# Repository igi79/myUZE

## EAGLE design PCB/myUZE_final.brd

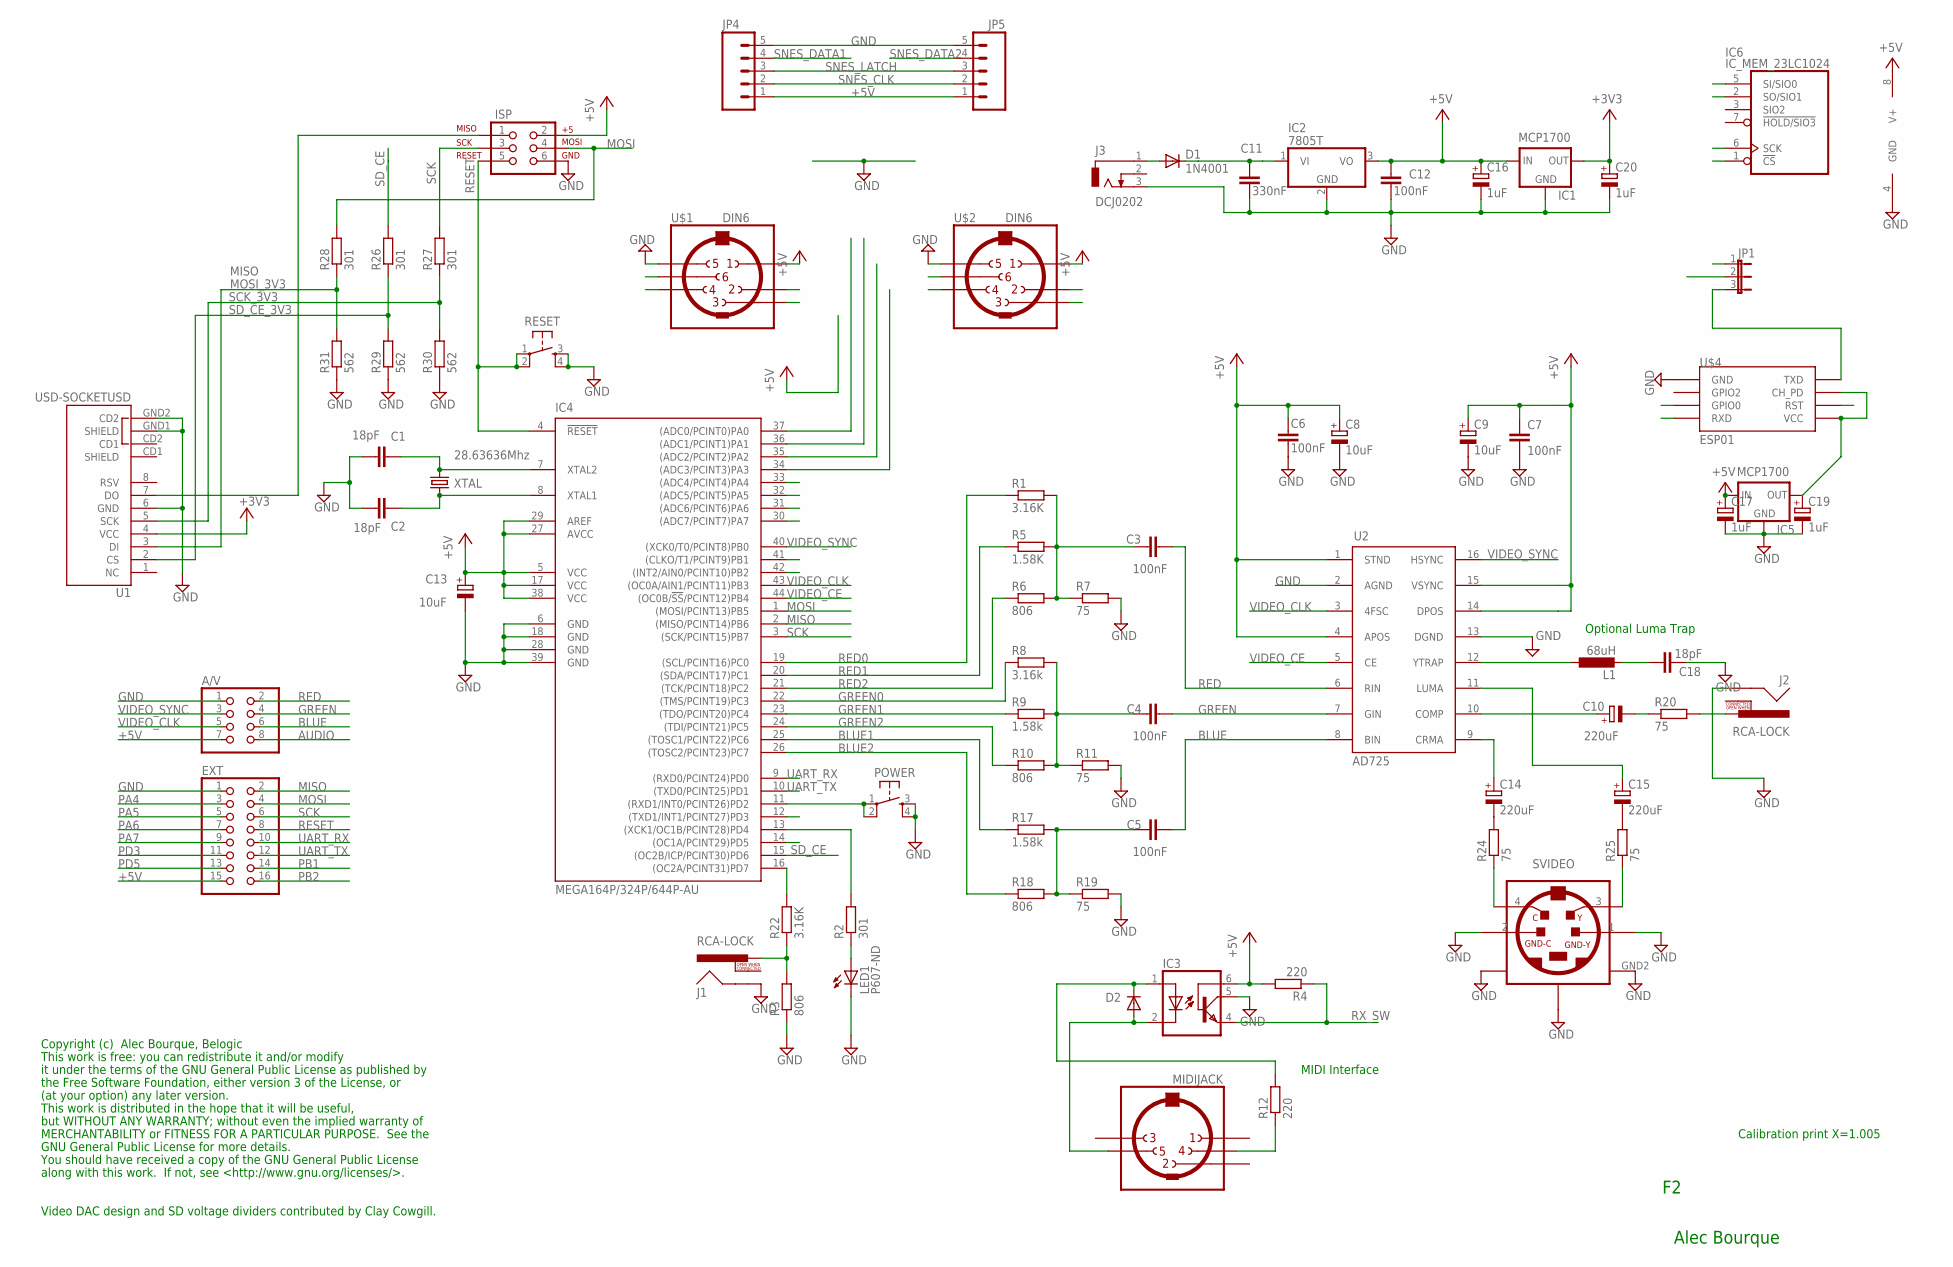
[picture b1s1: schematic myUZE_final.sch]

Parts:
A/V: PINHD-2X4; 2X04
AD725: AD725; SO16W
C1, C2, C18: 18pF; C0805
C3, C4, C5, C6, C7, C12: 100nF; C0805
C8, C9, C13: 10uF; 153CLV-0505
C10, C14, C15: 220uF; E2-5
C11: 330nF; C0805
C16, C17, C19, C20: 1uF; 153CLV-0505
D1: 1N4001; MELF-MLL41
D2: DIODE-MINIMELF; MINIMELF
EXT: PINHD-2X8; 2X08
IC1, IC5: MCP1700; TO92-INLINE
IC2: 7805T; TO220H
IC3: PC110; DIL06
IC4: MEGA164P/324P/644P-AU; TQFP44
IC6: IC_MEM_23LC1024; SOIC-8
ISP: AVR_SPI_PRG_6PTH; 2X3
J1, J2: RCA-LOCK; RCA_LOCK
J3: DCJ0202
JP1: JP2E; JP2
JP4, JP5: M05PTH; 1X05
L1: 68uH; IR-4
LED1: P607-ND; Q62902-B155
POWER: USER; TACTILE-PTH
R1, R22: 3.16K; R0805
R2, R26, R27, R28: 301; R0805
R3, R6, R10, R18: 806; R0805
R4, R12: 220; R0805
R5: 1.58K; R0805
R7, R11, R19, R20, R24, R25: 75; R0805
R8: 3.16k; R0805
R9, R17: 1.58k; R0805
R29, R30, R31: 562; R0805
RESET: RESET; TACTILE-PTH
SVIDEO: S-VIDEO OUT; MINIDIN4
U1: USD-SOCKETUSD; USD-SOCKET-PP
U$1, U$2: DIN6
U$4: ESP01
U$5: MIDIJACK; CP-2350
XTAL: 28.63636Mhz; HC49/S

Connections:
+3V3: C20.+, IC1.3 (OUT), U1.4 (VCC)
+5V: A/V.7, AD725.1 (STND), AD725.4 (APOS), AD725.14 (DPOS), AD725.15 (VSYNC), C6.1, C7.1, C8.+, C9.+, C12.1, C13.+, C16.+, C17.+, EXT.15, IC1.2 (IN), IC2.3 (VO), IC3.6 (BAS), IC4.5 (VCC), IC4.17 (VCC), IC4.27 (AVCC), IC4.29 (AREF), IC4.38 (VCC), IC5.2 (IN), IC6.8 (V+), ISP.2, JP4.1, JP5.1, R4.2, U$1.P1, U$2.P1
AUDIO: A/V.8, J1.PIN, R3.2, R22.1
BLUE: A/V.6, AD725.8 (BIN), C5.2
BLUE1: IC4.25 ((TOSC1/PCINT22)PC6), R17.1
BLUE2: IC4.26 ((TOSC2/PCINT23)PC7), R18.1
GND: A/V.1, AD725.2 (AGND), AD725.13 (DGND), C1.2, C2.2, C6.2, C7.2, C8.-, C9.-, C11.2, C12.2, C13.-, C16.-, C17.-, C18.2, C19.-, C20.-, EXT.1, IC1.1 (GND), IC2.2 (GND), IC3.5 (COL), IC4.6 (GND), IC4.18 (GND), IC4.28 (GND), IC4.39 (GND), IC5.1 (GND), IC6.4 (GND), ISP.6, J1.SHELL, J2.SHELL, J3.3, JP4.5, JP5.5, LED1.K (C), POWER.3, POWER.4, R3.1, R7.2, R11.2, R19.2, R29.1, R30.1, R31.1, RESET.3, RESET.4, SVIDEO.1 (GND-Y), SVIDEO.2 (GND-C), SVIDEO.GND1, SVIDEO.GND2, SVIDEO.GND3, U1.6 (GND), U1.GND1 (SHIELD), U1.GND2 (CD2), U$1.P5, U$2.P5, U$4.GND
GREEN: A/V.4, AD725.7 (GIN), C4.2
GREEN0: IC4.22 ((TMS/PCINT19)PC3), R8.1
GREEN1: IC4.23 ((TDO/PCINT20)PC4), R9.1
GREEN2: IC4.24 ((TDI/PCINT21)PC5), R10.1
MISO: EXT.2, IC4.2 ((MISO/PCINT14)PB6), IC6.2 (SO/SIO1), ISP.1, U1.7 (DO)
MOSI: EXT.4, IC4.1 ((MOSI/PCINT13)PB5), IC6.5 (SI/SIO0), ISP.4, R28.2
MOSI_3V3: R28.1, R31.2, U1.3 (DI)
unnamed: AD725.12 (YTRAP), L1.1
unnamed: C18.1, L1.2
unnamed: C5.1, R17.2, R18.2, R19.1
unnamed: C4.1, R8.2, R9.2, R10.2, R11.1
unnamed: C3.1, R1.2, R5.2, R6.2, R7.1
unnamed: C10.-, R20.1
unnamed: AD725.10 (COMP), C10.+
unnamed: J2.PIN, R20.2
unnamed: C1.1, IC4.7 (XTAL2), XTAL.2
unnamed: D1.A, J3.1
unnamed: C14.-, R24.2
unnamed: C2.1, IC4.8 (XTAL1), XTAL.1
unnamed: IC4.16 ((OC2A/PCINT31)PD7), R22.2
unnamed: D2.A, IC3.2 (C), U$5.5
unnamed: D2.C, IC3.1 (A), R12.2
unnamed: R12.1, U$5.4
unnamed: JP1.3, U$4.TX (TXD)
unnamed: C11.1, D1.C, IC2.1 (VI)
unnamed: C19.+, IC5.3 (OUT), U$4.CH_PD, U$4.VCC
unnamed: IC4.13 ((XCK1/OC1B/PCINT28)PD4), R2.2
unnamed: LED1.A, R2.1
unnamed: C15.-, R25.2
unnamed: AD725.11 (LUMA), C15.+
unnamed: AD725.9 (CRMA), C14.+
unnamed: R24.1, SVIDEO.4 (C)
unnamed: R25.1, SVIDEO.3 (Y)
PA4: EXT.3, IC4.33 ((ADC4/PCINT4)PA4), IC6.1 (!CS)
PA5: EXT.5, IC4.32 ((ADC5/PCINT5)PA5)
PA6: EXT.7, IC4.31 ((ADC6/PCINT6)PA6)
PA7: EXT.9, IC4.30 ((ADC7/PCINT7)PA7), U$4.GPIO0
PB1: EXT.14, IC4.41 ((CLKO/T1/PCINT9)PB1)
PB2: EXT.16, IC4.42 ((INT2/AIN0/PCINT10)PB2)
PD3: EXT.11, IC4.12 ((TXD1/INT1/PCINT27)PD3), U$4.RST
PD5: EXT.13, IC4.14 ((OC1A/PCINT29)PD5)
POWER_SW: IC4.11 ((RXD1/INT0/PCINT26)PD2), POWER.1, POWER.2
RED: A/V.2, AD725.6 (RIN), C3.2
RED0: IC4.19 ((SCL/PCINT16)PC0), R1.1
RED1: IC4.20 ((SDA/PCINT17)PC1), R5.1
RED2: IC4.21 ((TCK/PCINT18)PC2), R6.1
RESET: EXT.8, IC4.4 (!RESET), ISP.5, RESET.1, RESET.2
RX_SW: IC3.4 (EMI), JP1.1, R4.1
SCK: EXT.6, IC4.3 ((SCK/PCINT15)PB7), IC6.6 (SCK), ISP.3, R27.2
SCK_3V3: R27.1, R30.2, U1.5 (SCK)
SD_CE: IC4.15 ((OC2B/ICP/PCINT30)PD6), R26.2
SD_CE_3V3: R26.1, R29.2, U1.2 (CS)
SNES_CLK: IC4.34 ((ADC3/PCINT3)PA3), JP4.2, JP5.2, U$1.P2, U$2.P2
SNES_DATA1: IC4.37 ((ADC0/PCINT0)PA0), JP4.4, U$2.P4
SNES_DATA2: IC4.36 ((ADC1/PCINT1)PA1), JP5.4, U$1.P4
SNES_LATCH: IC4.35 ((ADC2/PCINT2)PA2), JP4.3, JP5.3, U$1.P3, U$2.P3
UART_RX: EXT.10, IC4.9 ((RXD0/PCINT24)PD0), JP1.2
UART_TX: EXT.12, IC4.10 ((TXD0/PCINT25)PD1), U$4.RX (RXD)
VIDEO_CE: AD725.5 (CE), IC4.44 ((OC0B/!SS!/PCINT12)PB4)
VIDEO_CLK: A/V.5, AD725.3 (4FSC), IC4.43 ((OC0A/AIN1/PCINT11)PB3)
VIDEO_SYNC: A/V.3, AD725.16 (HSYNC), IC4.40 ((XCK0/T0/PCINT8)PB0)

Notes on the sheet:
Optional Luma Trap
Alec Bourque
Copyright (c) Alec Bourque, Belogic
This work is free: you can redistribute it and/or modify
it under the terms of the GNU General Public License as published by
the Free Software Foundation, either version 3 of the License, or
(at your option) any later version.
This work is distributed in the hope that it will be useful,
but WITHOUT ANY WARRANTY; without even the implied warranty of
MERCHANTABILITY or FITNESS FOR A PARTICULAR PURPOSE. See the
GNU General Public License for more details.
You should have received a copy of the GNU General Public License
along with this work. If not, see <http://www.gnu.org/licenses/>.
MIDI Interface
Calibration print X=1.005
Video DAC design and SD voltage dividers contributed by Clay Cowgill.

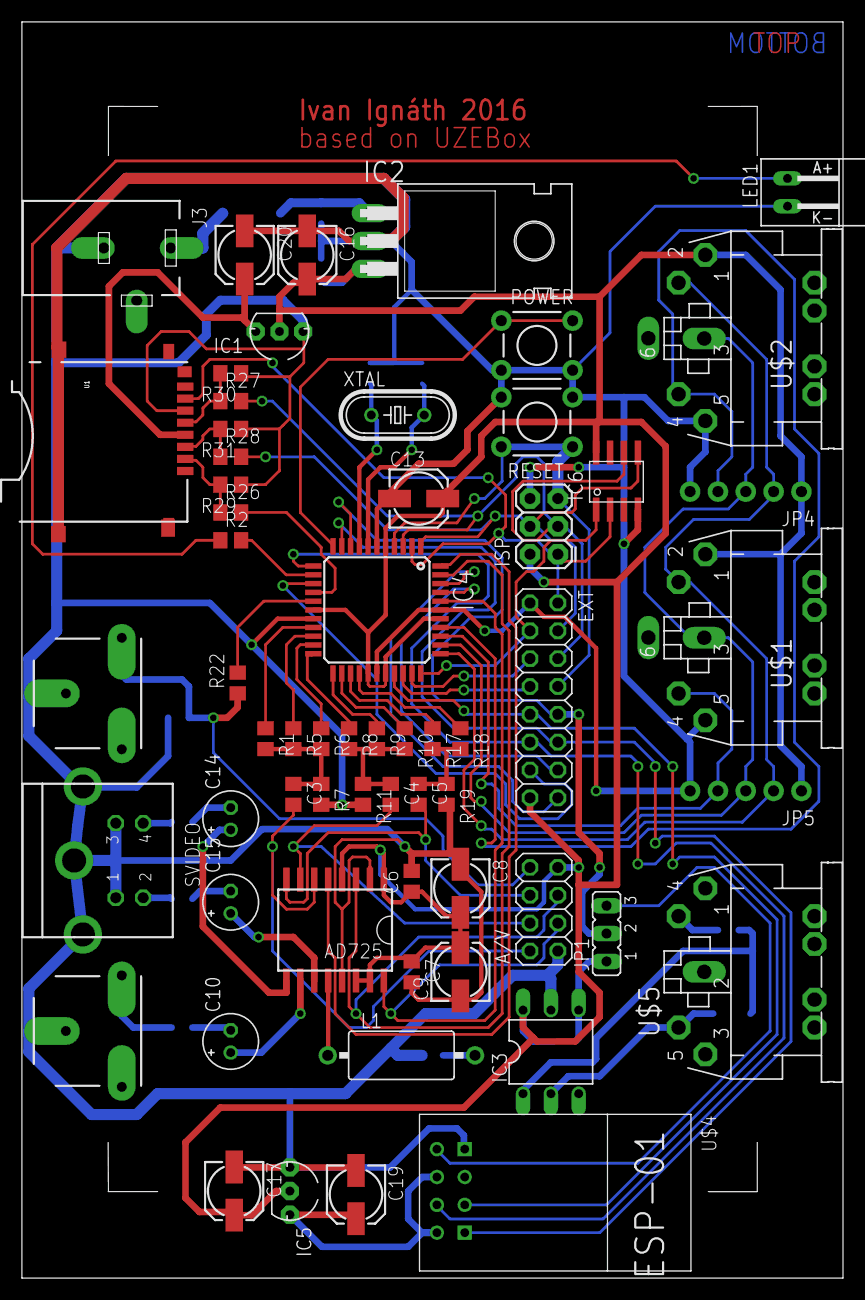
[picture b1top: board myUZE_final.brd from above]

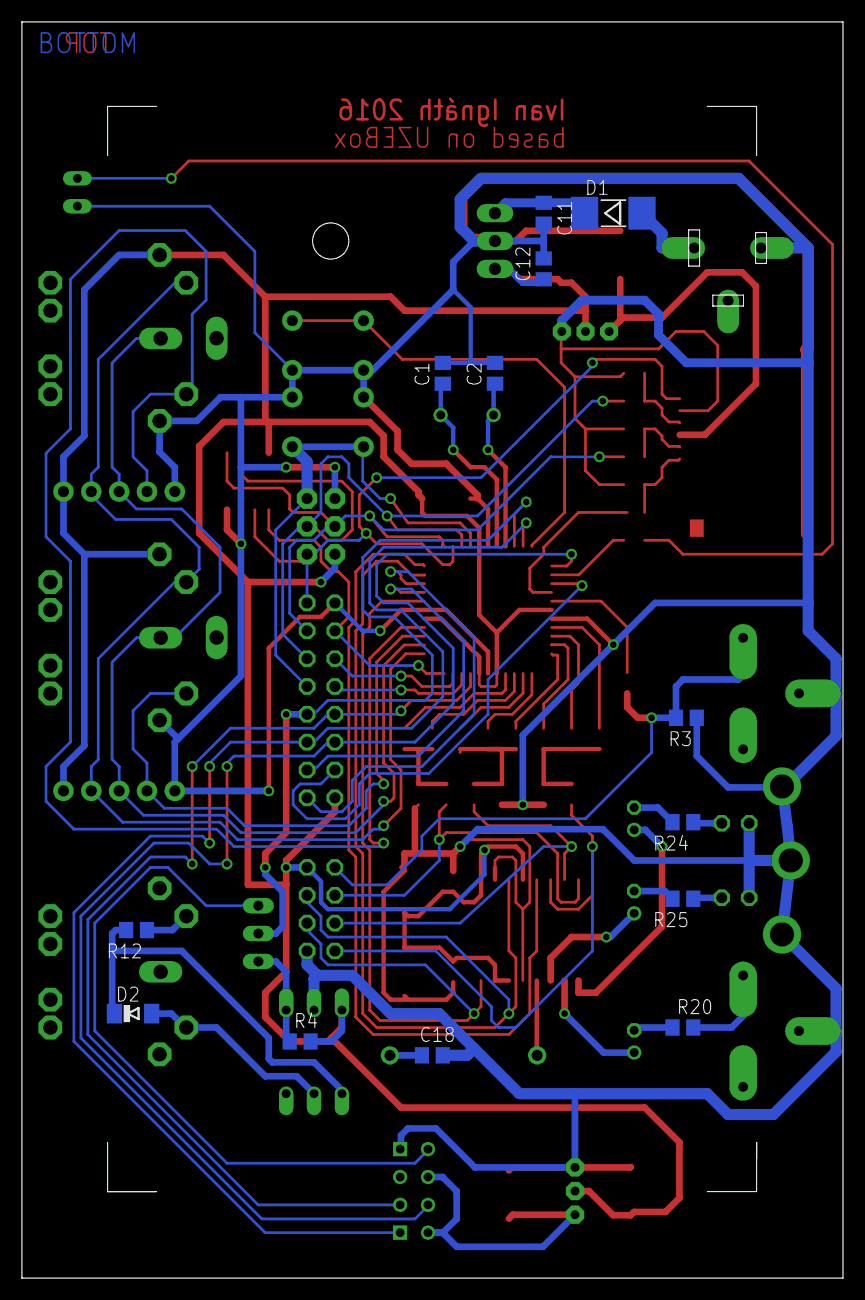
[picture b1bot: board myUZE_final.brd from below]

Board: 2 copper layers, 74.9 x 114.6 mm, 74 parts (13 on the bottom side), 68 nets.

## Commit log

2016-03-12 Final
2016-03-20 PCB in PDF

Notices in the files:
parts and their libraries:
SparkFun-Connectors-igi: Licensing: Creative Commons ShareAlike 4.0 International - https://creativecommons.org/licenses/by-sa/4.0
